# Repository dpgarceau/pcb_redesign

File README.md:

# AeroJudge PCB Redesign - Board Consolidation Project

**Goal:** Merge two existing boards plus three sub-modules into a single Raspberry Pi 4 HAT for streamlined production.

This project consolidates a multi-board assembly into one functional HAT PCB suitable for commercial manufacturing (JLCPCB-A or similar).

## Project Overview

Currently, the AeroJudge system consists of:
- Main board (primary interface and controls)
- Power board with three mounted sub-modules
- Multiple interconnecting cables

**Target:** Single PCB design with all functionality integrated, ready for automated assembly.

## Files Included

- `Main_Board.kicad_pcb` / `Main_Board.kicad_sch` - Primary interface board
- `Power_Board.kicad_pcb` / `Power_Board.kicad_sch` - Power management board
- `Pololu_2810_Circuit.pdf` - Circuit diagram for power switch implementation
- Sub-board reference links and datasheets (see below)

## Main Board Changes

**Components to Remove:**
- ENC 1 (keep ENC2 only)
- GPIO16, GPIO12, GPIO23, GPIO18
- All I2C connectors except I2C-1 (which will be integrated on-board)
- Backside pads for poweroff select and shutdown select (replace with direct traces to GPIO24 and GPIO25)

## Power Board Integration

The power board currently uses three separate sub-modules that must be integrated directly onto the main PCB:

### 1. INA226 Current/Voltage Sensor
- Reference module: https://www.aliexpress.us/item/3256806274363321.html
- Function: Battery monitoring
- Designer should integrate equivalent circuit based on INA226 datasheet

### 2. Pololu 2810 Power Switch
- Circuit diagram provided: `Pololu_2810_Circuit.pdf`
- Use this circuit diagram to integrate switch functionality onto main board
- No pre-made module needed

### 3. Voltage Regulator (Requires Redesign)
- Current setup uses manual voltage adjustment (not optimal)
- **Requirements:** 5.1V DC output, 3+ Amp capability for Raspberry Pi 4
- **Options:**
  - Clone Pololu 4892 circuit (5V, 3.4A Step-Down Voltage Regulator D30V30F)
  - Design equivalent buck converter circuit
  - Designer should recommend specific components/circuit

**Power Input:**
- Replace current battery solder pads with appropriate DC power connector/plug
- Specify connector type in design

**Connectors Being Eliminated:**
All external connectors between boards become internal traces:
- I2C connectors
- Power/shutoff connectors  
- 5V battery connector

## Additional Requirements

### LED Connector
- Duplicate existing LED connector
- Add second connector for 3.3V LED operation
- Designer should specify connector types

### Physical Constraints
- Base on Raspberry Pi 4 HAT form factor (can be larger if needed - maximum size without case redesign shown in `AeroJudge_PCB-Size.pdf`, provide size recommendations if that is not large enough)
- **Connector height limit:** Approximately 5mm (90-degree connectors required for case clearance)
- Components can be on both sides of board
- **Avoid placing connectors on bottom side** (HAT clearance requirements)
- Existing case can be redesigned if necessary, but prefer to work within current constraints

### Board Markings
- Front: AeroJudge logo, website link, "Board Rev 3.0"
- Rear: IMAC logo (if space permits, not critical)

## Deliverables Expected

1. Complete KiCad project files (schematics + PCB layout)
2. Manufacturing-ready Gerber files
3. Bill of Materials (BOM) with specific part numbers
4. Assembly drawing/notes
5. Board size recommendations based on component layout

## Design Notes

- Target manufacturer: JLCPCB-A or similar automated assembly service
- All sub-assemblies must be eliminated - single PCB only
- Maintain all existing functionality from current two-board system
- Designer should flag any potential issues with integration approach

## Questions for Designer

Before starting, please confirm:
1. Are the provided sub-board references sufficient, or do you need additional datasheets?
2. What board dimensions do you recommend based on component density?
3. Any concerns about the voltage regulator redesign requirements?

## Contact

For questions or clarifications during design process, please contact me through upwork.

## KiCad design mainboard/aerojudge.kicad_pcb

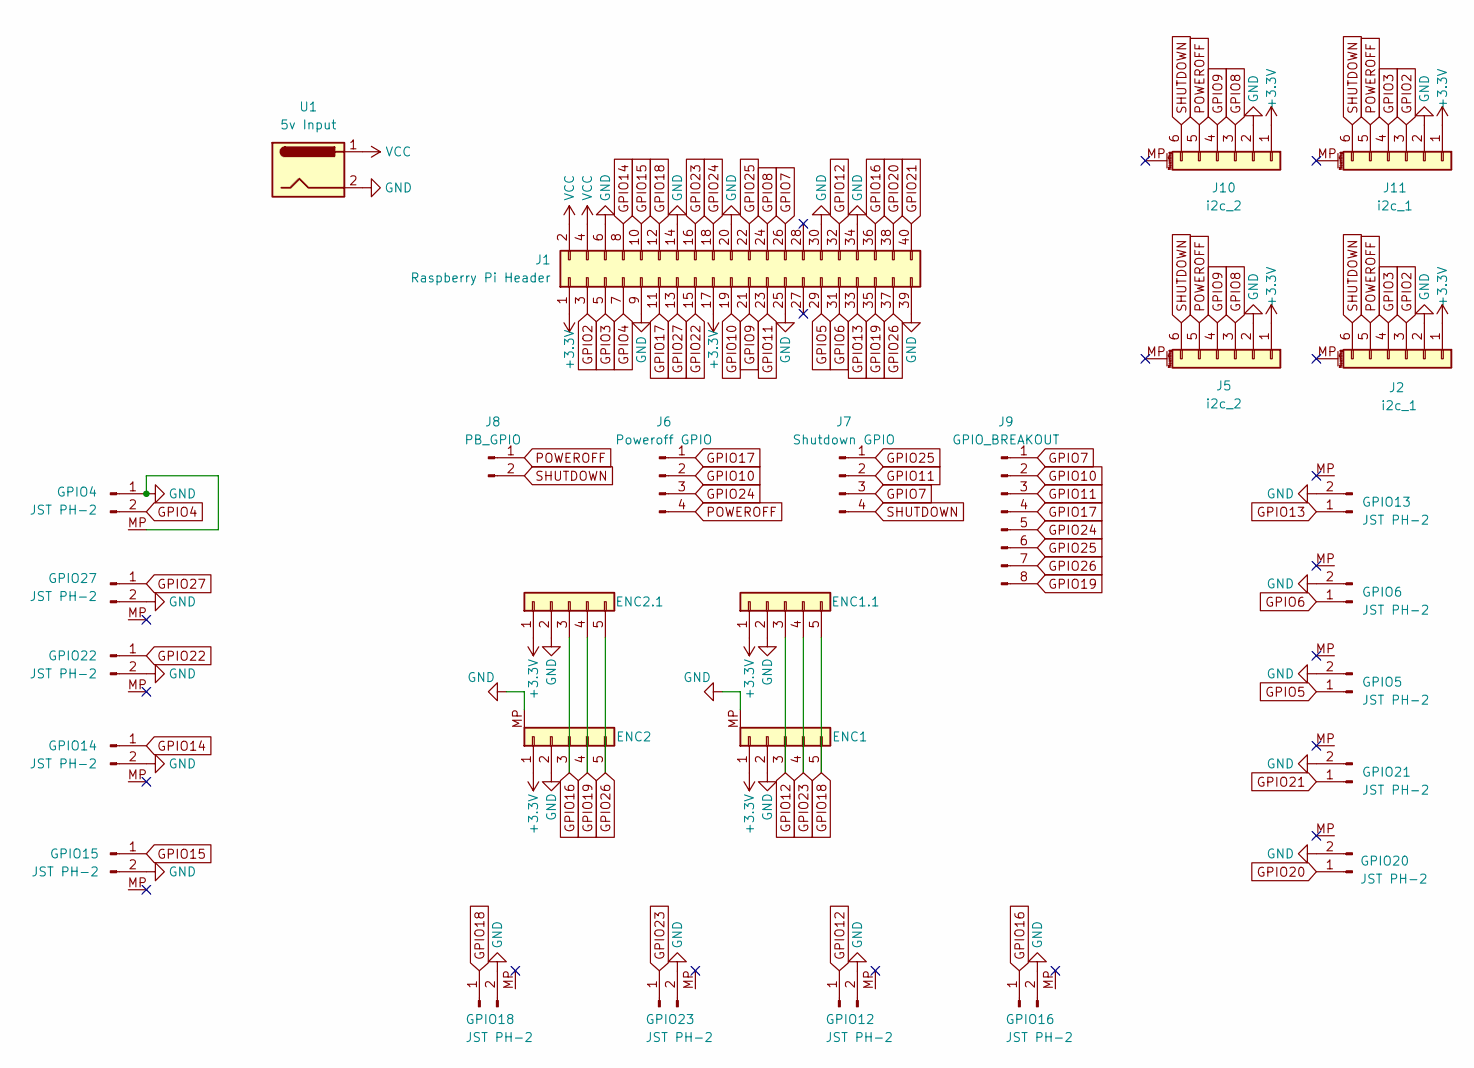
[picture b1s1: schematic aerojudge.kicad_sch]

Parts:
ENC1, ENC2: Encoder_2mm_1x5_MP; JST_PH_S5B-PH-SM4-TB_1x05-1MP_P2.00mm_Horizontal
ENC1.1, ENC2.1: Conn_01x05; PinHeader_1x05_P2.00mm_Vertical
GPIO4, GPIO5, GPIO6, GPIO12, GPIO13, GPIO14, GPIO15, GPIO16, GPIO18, GPIO20, GPIO21, GPIO22, GPIO23, GPIO27: JST PH-2; JST_PH_S2B-PH-K_1x02_P2.00mm_Horizontal_MP
J1: Raspberry Pi Header; PinHeader_2x20_P2.54mm_RPI
J2: i2c_1; JST_PH_S6B-PH-SM4-TB_1x06-1MP_P2.00mm_Horizontal
J5: i2c_2; JST_PH_S6B-PH-SM4-TB_1x06-1MP_P2.00mm_Horizontal
J6: Poweroff GPIO; SolderJumperSelector_3PIN_P3_Default
J7: Shutdown GPIO; SolderJumperSelector_3PIN_P1_Default
J8: PB_GPIO; PinHeader_1x02_P2.00mm_Vertical
J9: GPIO_BREAKOUT; PinHeader_2x04_P1.27mm_Vertical_SMD_NoBorder
J10: i2c_2; JST_SH_SM06B-SRSS-TB_1x06-1MP_P1.00mm_Horizontal
J11: i2c_1; JST_SH_SM06B-SRSS-TB_1x06-1MP_P1.00mm_Horizontal
U1: 5v Input; Solder_Pads

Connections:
+3.3V: ENC1.1, ENC1.1.1, ENC2.1, ENC2.1.1, J1.1, J1.17, J2.1, J5.1, J10.1, J11.1
GND: ENC1.2, ENC1.MP, ENC1.1.2, ENC2.2, ENC2.MP, ENC2.1.2, GPIO4.1, GPIO4.MP, GPIO5.2, GPIO6.2, GPIO12.2, GPIO13.2, GPIO14.2, GPIO15.2, GPIO16.2, GPIO18.2, GPIO20.2, GPIO21.2, GPIO22.2, GPIO23.2, GPIO27.2, J1.6, J1.9, J1.14, J1.20, J1.25, J1.30, J1.34, J1.39, J2.2, J5.2, J10.2, J11.2, U1.2
GPIO2: J1.3, J2.3, J11.3
GPIO3: J1.5, J2.4, J11.4
GPIO4: GPIO4.2, J1.7
GPIO5: GPIO5.1, J1.29
GPIO6: GPIO6.1, J1.31
GPIO7: J1.26, J7.3, J9.1
GPIO8: J1.24, J5.3, J10.3
GPIO9: J1.21, J5.4, J10.4
GPIO10: J1.19, J6.2, J9.2
GPIO11: J1.23, J7.2, J9.3
GPIO12: ENC1.3, ENC1.1.3, GPIO12.1, J1.32
GPIO13: GPIO13.1, J1.33
GPIO14: GPIO14.1, J1.8
GPIO15: GPIO15.1, J1.10
GPIO16: ENC2.3, ENC2.1.3, GPIO16.1, J1.36
GPIO17: J1.11, J6.1, J9.4
GPIO18: ENC1.5, ENC1.1.5, GPIO18.1, J1.12
GPIO19: ENC2.4, ENC2.1.4, J1.35, J9.8
GPIO20: GPIO20.1, J1.38
GPIO21: GPIO21.1, J1.40
GPIO22: GPIO22.1, J1.15
GPIO23: ENC1.4, ENC1.1.4, GPIO23.1, J1.16
GPIO24: J1.18, J6.3, J9.5
GPIO25: J1.22, J7.1, J9.6
GPIO26: ENC2.5, ENC2.1.5, J1.37, J9.7
GPIO27: GPIO27.1, J1.13
POWEROFF: J2.5, J5.5, J6.4, J8.1, J10.5, J11.5
SHUTDOWN: J2.6, J5.6, J7.4, J8.2, J10.6, J11.6
VCC: J1.2, J1.4, U1.1

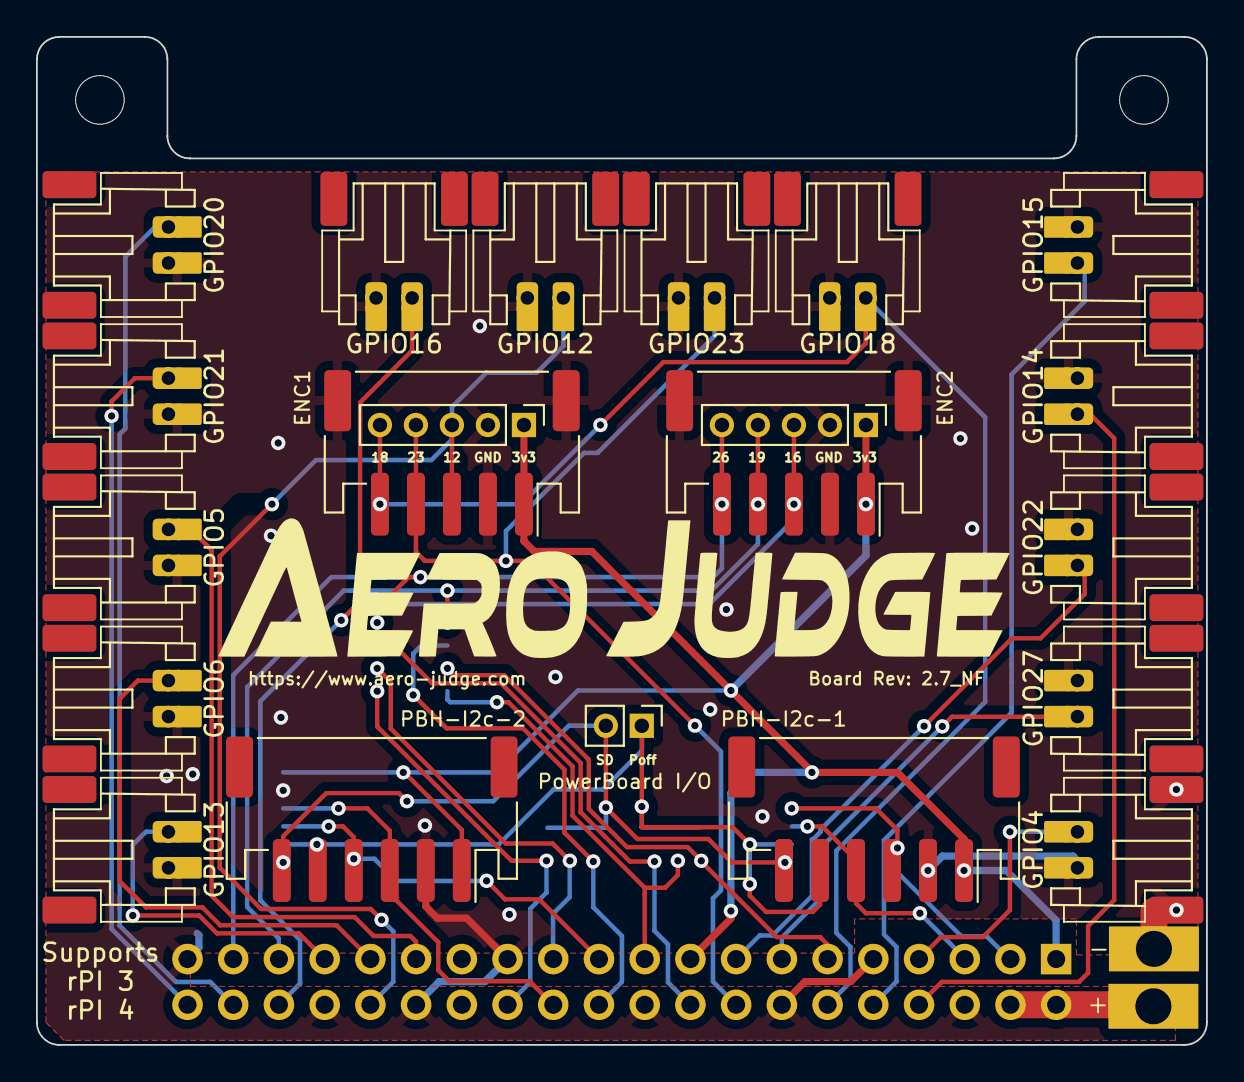
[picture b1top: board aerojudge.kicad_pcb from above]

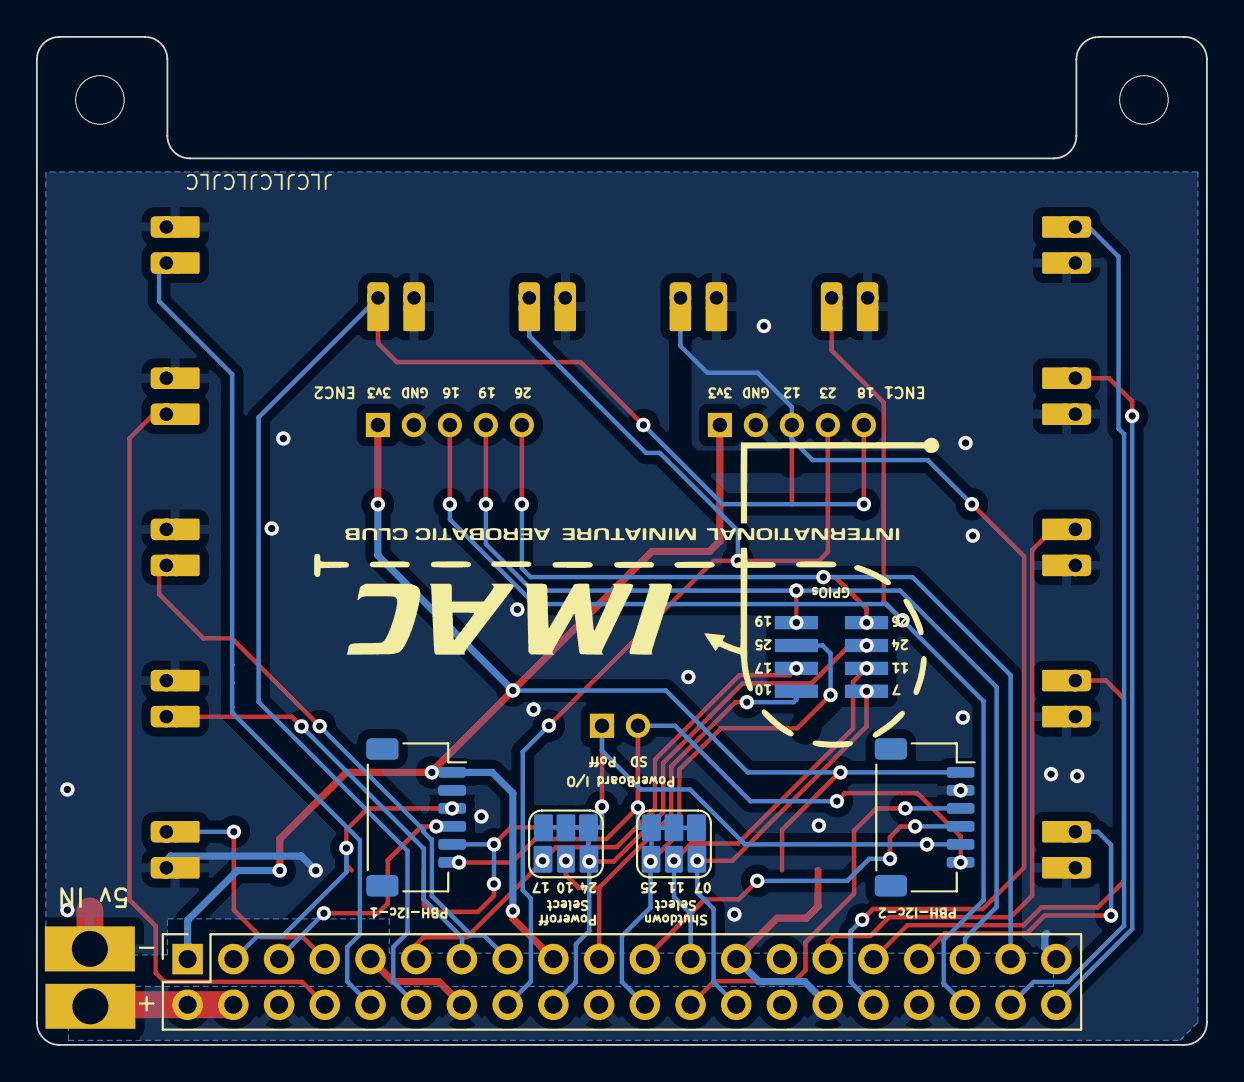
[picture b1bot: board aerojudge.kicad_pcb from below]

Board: 2 copper layers, 65.0 x 56.0 mm, 30 parts (7 on the bottom side), 31 nets.

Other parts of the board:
AEROJUDGE_LOGO: LOGO; AEROJUDGE_LOGO
IMAC_LOGO: LOGO; IMAC_LOGO

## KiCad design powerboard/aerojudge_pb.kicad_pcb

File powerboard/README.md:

# AeroJudge PCB

<picture>
  <source
    srcset="../..//Media/AeroJudge%20Logo/AeroJudge%20Logo.jpg"
    media="(orientation: landscape)" />
  
</picture>
<br>

Here you will find details and source files for the aerojudge powerboard PCB.  This PCB is used to house the power components of the device.

<picture>
  <source
    srcset="AeroJudge_Powerboard_PCB_Top.png"
    media="(orientation: landscape)" />
  
</picture>
<picture>
  <source
    srcset="AeroJudge_Powerboard_PCB_Bottom.png"
    media="(orientation: landscape)" />
  
</picture>
<br>

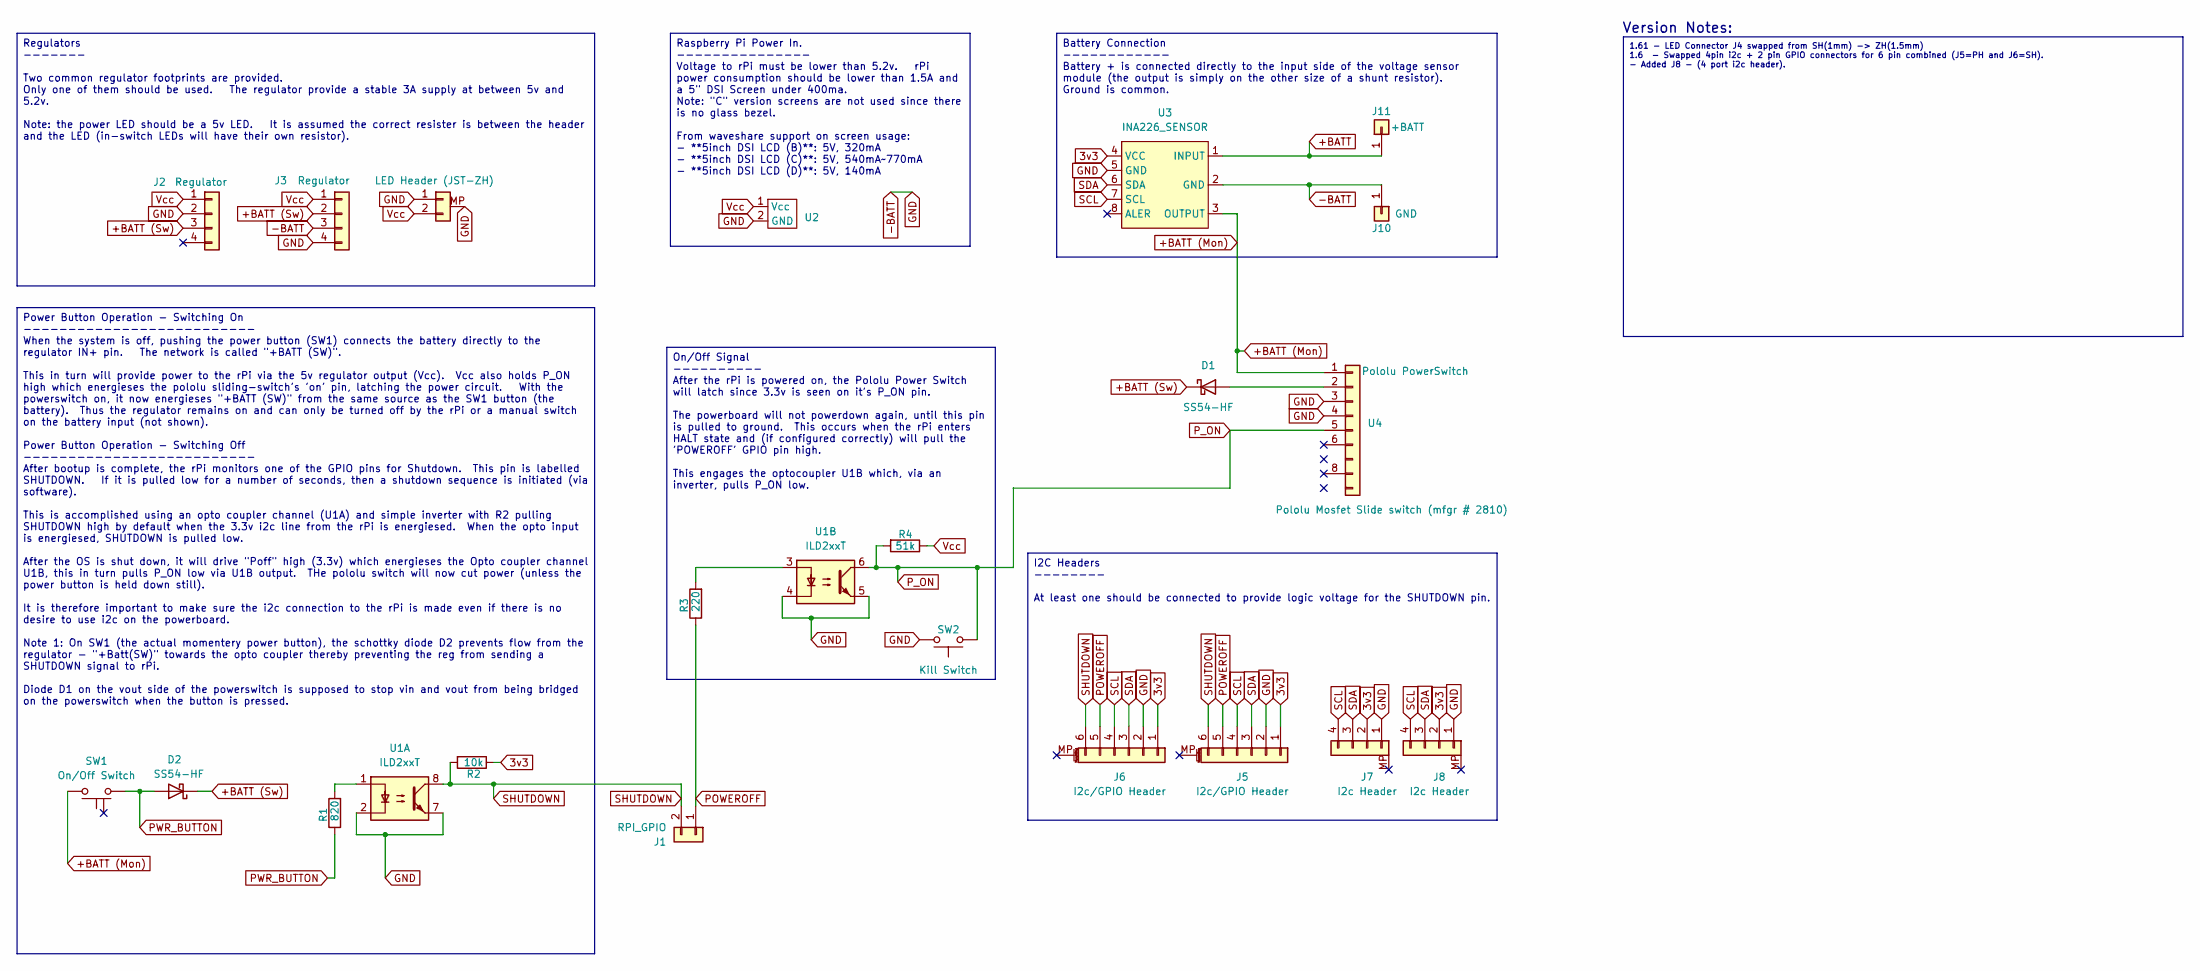
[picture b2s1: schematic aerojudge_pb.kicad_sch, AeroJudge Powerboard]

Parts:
D1, D2: SS54-HF; D_SMA
J1: RPI_GPIO; SolderJumper-2_P2.54mm_Open_Pad2.0x2.5mm
J2: Regulator; PinHeader_1x04_P2.54mm_Vertical_NoBorder
J3: Regulator; MP1584EN_Regulator
J4: LED Header (JST-ZH); JST_ZH_B2B-ZR-SM4-TF_1x02-1MP_P1.50mm_Vertical
J5: I2c/GPIO Header; JST_PH_B6B-PH-SM4-TB_1x06-1MP_P2.00mm_Vertical
J6: I2c/GPIO Header; JST_SH_BM06B-SRSS-TB_1x06-1MP_P1.00mm_Vertical
J7, J8: I2c Header; JST_SH_SM04B-SRSS-TB_1x04-1MP_P1.00mm_Horizontal
J10: GND; TestPoint_Pad_4.0x4.0mm
J11: +BATT; TestPoint_Pad_4.0x4.0mm
R1: 820; R_1206_3216Metric
R2: 10k; R_1206_3216Metric
R3: 220; R_1206_3216Metric
R4: 51k; R_1206_3216Metric
SW1: On/Off Switch; JST_PH_B2B-PH-SM4-TB_1x02-1MP_P2.00mm_Vertical
SW2: Kill Switch; SW_Push_SPST_NO_Alps_SKRK
U1: ILD2xxT; SOIC-8_6.6x6.27mm_P1.27mm
U2: Solder_Pads
U3: INA226_SENSOR
U4: Pololu PowerSwitch; Mini MOSFET Slide Switch

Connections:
3v3: J5.1, J6.1, J7.2, J8.2, R2.1, U3.4 (VCC)
+BATT: J11.1, U3.1 (INPUT)
+BATT (Mon): SW1.2, U3.3 (OUTPUT), U4.1
+BATT (Sw): D1.1 (K), D2.1 (K), J2.3, J3.2
-BATT: J2.2, J3.3, J3.4, J4.1, J4.MP, J5.2, J6.2, J7.1, J8.1, J10.1, SW2.2, U1.2, U1.4, U1.5, U1.7, U2.2 (GND), U3.2 (GND), U3.5 (GND), U4.3, U4.4
unnamed: D1.2 (A), U4.2
unnamed: R1.2, U1.1
unnamed: R3.2, U1.3
POWEROFF: J1.1, J5.5, J6.5, R3.1
PWR_BUTTON: D2.2 (A), R1.1, SW1.1
P_ON: R4.2, SW2.1, U1.6, U4.5
SCL: J5.4, J6.4, J7.4, J8.4, U3.7 (SCL)
SDA: J5.3, J6.3, J7.3, J8.3, U3.6 (SDA)
SHUTDOWN: J1.2, J5.6, J6.6, R2.2, U1.8
Vcc: J2.1, J3.1, J4.2, R4.1, U2.1 (Vcc)

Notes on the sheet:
Version Notes:
Battery Connection ------------ Battery + is connected directly to the input side of the voltage sensor module (the output is simply on the other size of a shunt resistor). Ground is common.
I2C Headers -------- At least one should be connected to provide logic voltage for the SHUTDOWN pin.
Regulators ------- Two common regulator footprints are provided. Only one of them should be used. The regulator provide a stable 3A supply at between 5v and 5.2v. Note: the power LED should be a 5v LED. It is assumed the correct resister is between the header and the LED (in-switch LEDs will have t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
Power Button Operation - Switching On -------------------------- When the system is off, pushing the power button (SW1) connects the battery directly to the regulator IN+ pin. The network is called "+BATT (SW)". This in turn will provide power to the rPi via the 5v regulator output (Vcc). Vcc also 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
1.61 - LED Connector J4 swapped from SH(1mm) -> ZH(1.5mm) 1.6 - Swapped 4pin i2c + 2 pin GPIO connectors for 6 pin combined (J5=PH and J6=SH). - Added J8 - (4 port i2c header).
On/Off Signal ---------- After the rPi is powered on, the Pololu Power Switch will latch since 3.3v is seen on it's P_ON pin. The powerboard will not powerdown again, until this pin is pulled to ground. This occurs when the rPi enters HALT state and (if configured correctly) will pull the 'POWEROFF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
Raspberry Pi Power In. --------------- Voltage to rPi must be lower than 5.2v. rPi power consumption should be lower than 1.5A and a 5" DSI Screen under 400ma. Note: "C" version screens are not used since there is no glass bezel. From waveshare support on screen usage: - **5inch DSI LCD (B)**: 5V, 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

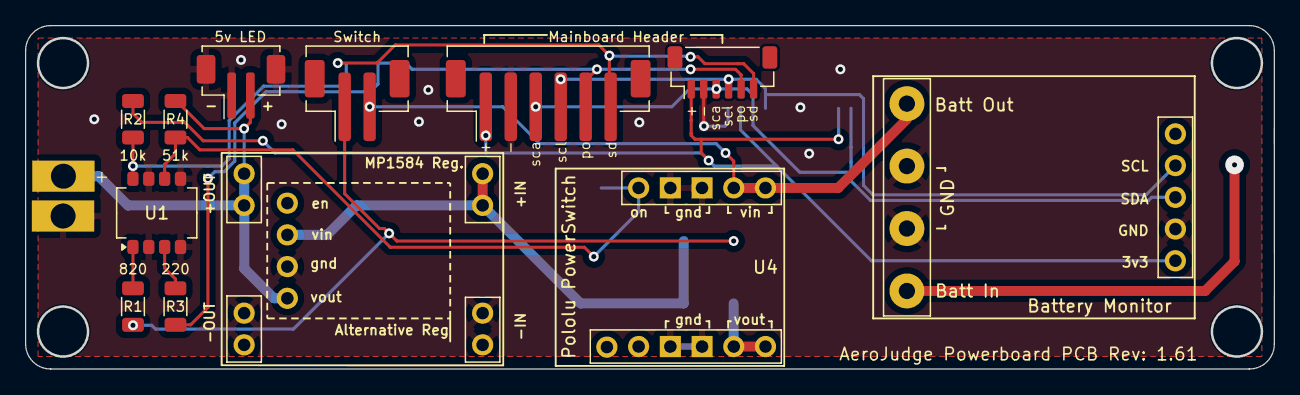
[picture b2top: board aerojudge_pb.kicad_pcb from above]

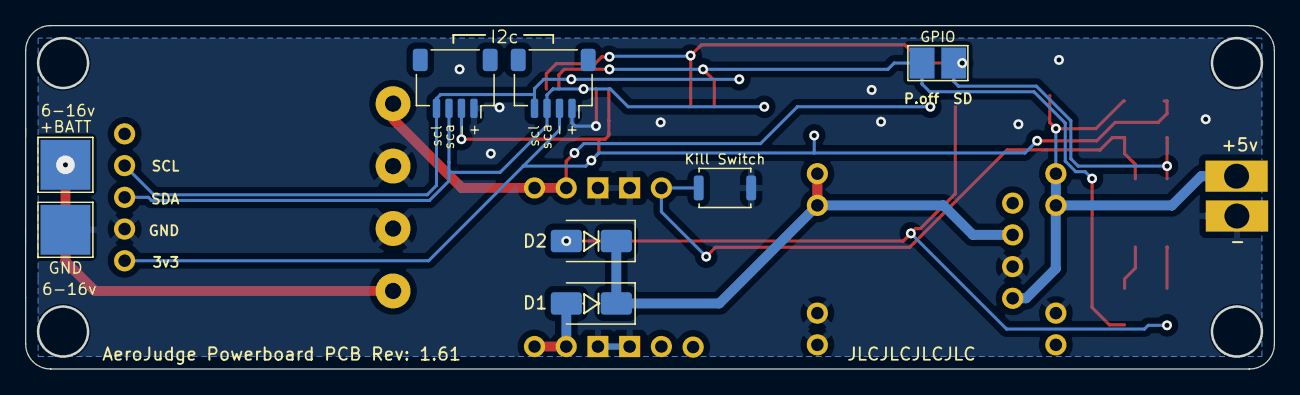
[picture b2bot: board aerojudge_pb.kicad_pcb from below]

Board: 2 copper layers, 100.0 x 27.5 mm, 22 parts (9 on the bottom side), 15 nets.

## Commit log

2025-10-25 Add mainpcb section to readme
2025-10-25 Add initial readme file to powerboard directory
2025-10-25 Enhance README with detailed project specifications
    Expanded project description and clarified design requirements for the PCB redesign.
2025-10-25 Clarify component removal instructions in README
    Updated the README to clarify component removal on the main board.
2025-10-26 Update README with new board design specifications
    Added details about the new main board design and connector requirements.
2025-10-26 Remove ToDo section from README
    Removed ToDo section from README.
2025-10-26 Add link to INA226_Sensor in README
    Updated the description of the INA226_Sensor to include a link.
2025-10-26 Remove cost impact question from README
    Removed a question regarding estimated component cost impact from the README.
2025-10-26 Update physical constraints for PCB size recommendations
    Clarified maximum size constraints for PCB design.
2025-11-13 Single Schematic (Draft) and XT30PW-M Specs
2025-12-06 Updated Layout guide for developer
